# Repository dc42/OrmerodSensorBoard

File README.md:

OrmerodSensorBoard
==================

Here are the design files for my Z-height sensor board add-on to the RepRapPro Ormerod 3D printer. This board replaces the original IR sensor board used for Z-probing. It has the following advantages over the original:

1. It uses modulated infrared light, which makes it much less sensitive to ambient infrared such as is found in sunlight and in incandescent artificial light.
2. The sensor board is mounted on the hot end so that the sensor head is in-line with the nozzle in the x-direction. This makes it much less sensitive to variations in head sag.
3. The board includes the facility to mount the hot end connectors, eliminating the need for the original 6-pin connector. The new connectors are more reliable and more easily disassembled. In particular, the crimp receptacles can more easily be removed from the connector shell.
4. The board can accommodate three Cree LEDs to direct light on the work being printed. Alternatively, it can provide 12V power to an LED strip, or a constant-current supply to external LEDs.
5. The board includes provision for thermostatic control of the hot end fan. The fan is turned on when the hot end temperature exceeds approximately 42C, or when the board detects a hot end temperature measurement fault.
6. The board can also support an experimental ultrasonic sensor. This allows z-probing to be done anywhere on the bed. Due to variation in the speed of sound with temperature, the ultrasonic sensor is a little temperature-sensitive, but this can be compensated in the firmware.

Work is in progress to adapt the board for capacitive height sensing.

For assembly and usage instructions, please visit: http://miscsolutions.wordpress.com/assembling-and-using-the-eschertech-ormerod-hot-end-board/

I supply bare boards, kits of parts with all SMD components ready-mounted, and fully assembled boards. Contact me via the RepRap Ormerod forum at http://forums.reprap.org/list.php?340 by sending a personal message to dc42.

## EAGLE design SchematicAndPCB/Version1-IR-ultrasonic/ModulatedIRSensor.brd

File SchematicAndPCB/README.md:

Licence and copyright
=====================

Copyright (c) 2015 Escher Technologies Limited. Licensed under the Creative Commons Attribution-NonCommercial 4.0 license.
See https://creativecommons.org/licenses/by-nc/4.0/legalcode for a copy.

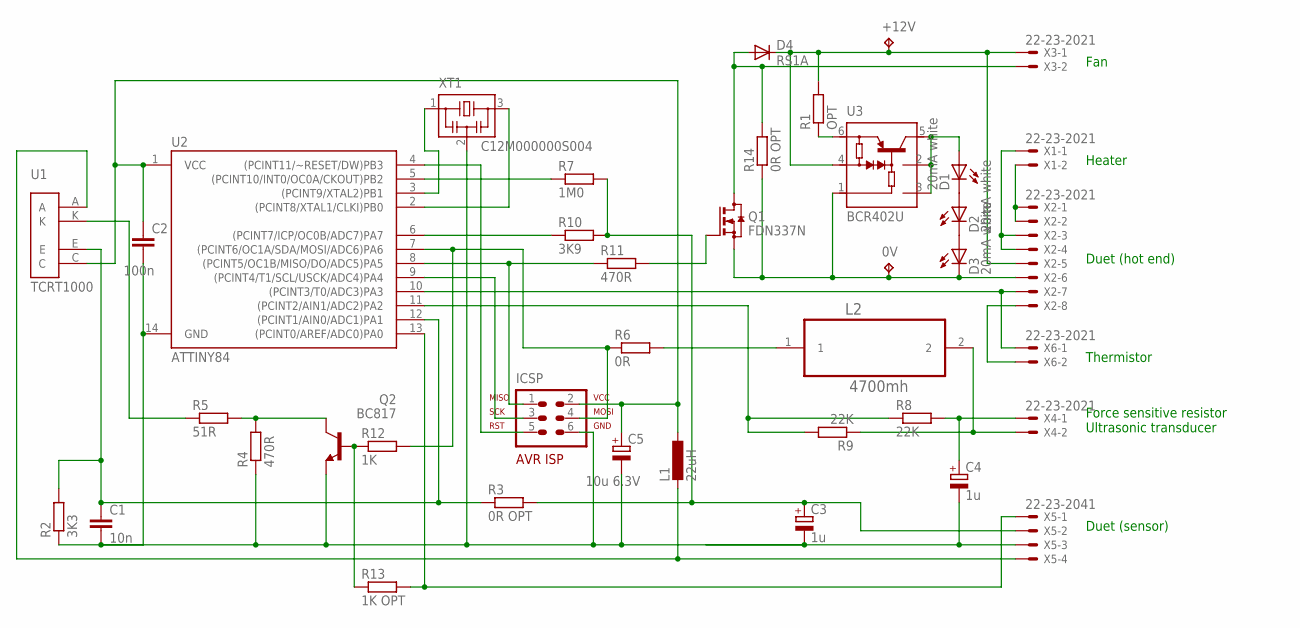
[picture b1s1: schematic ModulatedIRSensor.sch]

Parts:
0V: TPPAD1-13; P1-13
+12V: TPPAD1-13; P1-13
C1: 10n; C0603
C2: 100n; C0603
C3, C4: 1u; SMC_A
C5: 10u 6.3V; SMC_A
D1, D2, D3: 20mA white; LED5MM
D4: RS1A; DO214AC
ICSP: AVR-ISP-6VERT; AVR-ISP-6
L1: 22uH; L2012C
L2: 4700mh; INDC5650X530N
Q1: FDN337N; SOT23
Q2: BC817; SOT23
R1: OPT; R0603
R2: 3K3; R0603
R3, R14: 0R OPT; R0603
R4, R11: 470R; R0603
R5: 51R; R0603
R6: 0R; R0603
R7: 1M0; R0603
R8, R9: 22K; R0603
R10: 3K9; R0603
R12: 1K; R0603
R13: 1K OPT; R0603
U1: TCRT1000
U2: ATTINY84; SO14
U3: BCR402U; SC74_INFINEON
X1, X3, X4, X6: 22-23-2021
X2: 22-23-2021; 22-23-2081
X5: 22-23-2041
XT1: C12M000000S004; CSTCR6M

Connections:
GND: C1.2, C2.2, C3.-, C4.-, C5.-, ICSP.6, Q2.2 (E), R2.1, R4.1, U2.14 (GND), X5.3, XT1.2
GND2: 0V.TP, D3.K (C), Q1.2 (S), R14.1, U3.1 (GND), X2.6
LED: D1.A, U3.2 (IOUT2), U3.3 (IOUT3), U3.5 (IOUT1)
unnamed: L1.2, U1.A, X5.4
unnamed: L2.2, R9.1, X4.2
unnamed: ICSP.5, U2.4 ((PCINT11/~RESET/DW)PB3)
unnamed: ICSP.1, R11.1, U2.8 ((PCINT5/OC1B/MISO/DO/ADC5)PA5)
unnamed: ICSP.3, U2.9 ((PCINT4/T1/SCL/USCK/ADC4)PA4)
unnamed: ICSP.4, R6.1, R12.2, U2.7 ((PCINT6/OC1A/SDA/MOSI/ADC6)PA6)
unnamed: R1.1, U3.6 (REXT)
unnamed: D1.K (C), D2.A
unnamed: U2.10 ((PCINT3/T0/ADC3)PA3), X2.7, X6.1
unnamed: X1.2, X2.1, X2.2
unnamed: D2.K (C), D3.A
unnamed: C3.+, R3.2, R7.2, R10.2, X5.2
unnamed: D4.A, Q1.3 (D), R14.2, X3.2
unnamed: X1.1, X2.3, X2.4
unnamed: X2.8, X6.2
unnamed: R5.1, U1.K
unnamed: L2.1, R6.2
unnamed: Q2.3 (C), R4.2, R5.2
unnamed: R7.1, U2.5 ((PCINT10/INT0/OC0A/CKOUT)PB2)
unnamed: C4.+, R8.2, X4.1
unnamed: R10.1, U2.6 ((PCINT7/ICP/OC0B/ADC7)PA7)
unnamed: R8.1, R9.2, U2.11 ((PCINT2/AIN1/ADC2)PA2)
unnamed: Q1.1 (G), R11.2
unnamed: Q2.1 (B), R12.1, R13.1
unnamed: C1.1, R2.2, R3.1, U1.E, U2.12 ((PCINT1/AIN0/ADC1)PA1)
unnamed: R13.2, U2.13 ((PCINT0/AREF/ADC0)PA0), X5.1
unnamed: U2.2 ((PCINT8/XTAL1/CLKI)PB0), XT1.3
unnamed: U2.3 ((PCINT9/XTAL2)PB1), XT1.1
VCC: C2.1, C5.+, ICSP.2, L1.1, U1.C, U2.1 (VCC)
VS+12V: +12V.TP, D4.C, R1.2, U3.4 (VIN), X2.5, X3.1

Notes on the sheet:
Heater
Duet (hot end)
Thermistor
Duet (sensor)
Force sensitive resistor Ultrasonic transducer
Fan
TCRT1000

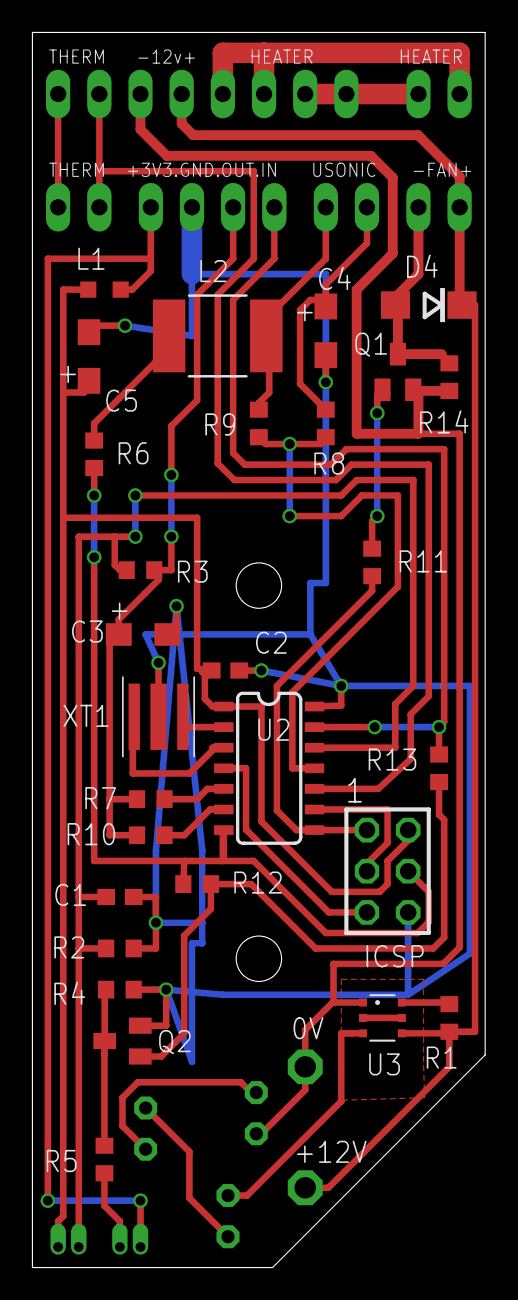
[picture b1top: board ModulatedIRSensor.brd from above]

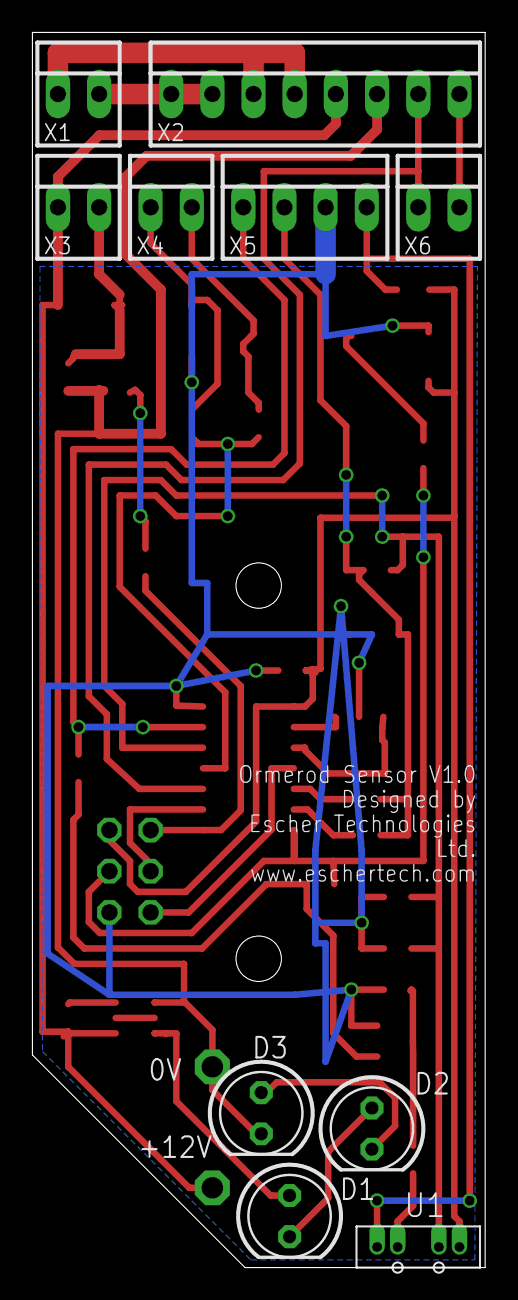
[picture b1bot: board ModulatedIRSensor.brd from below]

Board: 2 copper layers, 27.9 x 76.2 mm, 40 parts (12 on the bottom side), 33 nets.

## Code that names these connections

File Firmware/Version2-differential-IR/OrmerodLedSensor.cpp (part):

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#endif

#define DUAL_NOZZLE (1)		// set nonzero for dual nozzle support
#define ISR_DEBUG	(0)		// set nonzero to use PB2 as debug output pin

#if DUAL_NOZZLE && ISR_DEBUG
#error "DUAL_NOZZLE and ISR_DEBUG may not both be set"
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#define BITVAL(_x) static_cast<uint8_t>(1u << (_x))

// Pin assignments:
// PA0/ADC0		digital input from Duet
// PA1/ADC1		analog input from phototransistor
// PA2/ADC2		output to Duet via 12K resistor (single nozzle) OR analog input from thermistor2 (dual nozzle)
// PA3/ADC3		analog input from thermistor (single nozzle) or 1K/4K7 sense pin (dual nozzle)
// PA4/SCLK		1K/4K7 sense pin (single nozzle) or analog input from thermistor 1 (dual nozzle). Also SCLK when programming.
// PA5/OC1B		digital output to control fan, active high. Also MISO when programming.
// PA6/OC1A		near LED drive, active low in prototype, will be active high in release. Also MOSI when programming.
// PA7/OC0B		output to Duet via 10K resistor

// PB0			far LED drive, active high
// PB1			far LED drive, active high (paralleled with PB0)
// PB2/OC0A		unused (single nozzle) OR ISR-DEBUG pin OR output to Duet via 12K resistor (dual nozzle)
// PB3/RESET	not available, used for programming

__fuse_t __fuse __attribute__((section (".fuse"))) = {0xE2u, 0xDFu, 0xFFu};

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
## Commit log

2014-03-16 Added STL files
    Added STL files for the printed parts needed to use the new sensor
    board, along with some other printed parts for the Ormerod
2014-03-16 Replaced readme.txt by readme.md
2014-03-16 Added schematic, board layout and circuit notes
2014-03-20 Added fan deflector aerofoil
2014-03-22 Added firmware files
2014-03-24 Added new parts
2014-03-26 Updated BOM
2014-03-27 Added insulator that holds ultrasonic transducer
2014-03-27 Update readme.md
    Added description of insulator with holder for the ultrasonic transducer
2014-03-28 Changed insulator for ultrasonic transducer
    Modified the design of the insulator with a holder for the ultrasonic
    transducer to reduce the depth of the countersink, so that the screws
    only protrude 3mm beyond the back of the PCB. Added a cutout to allow
    in-situ programming.
2014-04-04 Added sensorpad.scad and .stl
2014-04-04 Added description of sensorpad.stl to readme file
2014-05-04 Added modified sensor pad and button push
    Added a modified version of the add-on sensor pad that places the homing
    tab nearer the z-screw and avoids fouling the z stepper motor shaft
2014-05-29 Added cutout to access ICSP contacts
    Added a cutout to the insulator so that the ICSP contacts for
    reprogramming the mcu can be accessed in-situ.
2014-05-29 Added capsense variant of the insulator
    Added a variant of the sensor board insulator to suit the prototype
    (hacked) capacitive height sensing board
2014-05-29 Add X-carriage design
    Added .scad and .stl files for Ormerod X-carriage
2014-06-19 Added sensor pad for diff IR sensor
    Also deleted some obsolete files
2014-06-20 Various parts updated
    Reduced tab width for differential IR sensor pad
    Adjusted spacing for differential IR sensor board holder
    Tidied up fan inlet duct and made some dimensions configurable
2014-06-23 Added nozzle mount
2014-06-24 Added differential LED board schematic
2014-06-24 Nozzle mount now configured for 2 nozzles
2014-06-26 Added revised modified heatsink duct
    Added new version of modified heatsink duct based on importing RRP's
    original one into OpenScad. Also made sensor pad 1mm wider.
2014-07-04 Rearranged folders and added diff LED firmware
2014-07-04 Added differential LED sensor circuit notes
2014-07-10 Corrected nozzle mount and added fan duct
    Increased the size of the slots in the nozzle mount to clear the brass
    Bowden end
    Added modified-fan-duct, which is RRP's fan duct with the cable tie loop
    cut off (the cable tie loop gets in the way of my hot end board)
2014-07-10 Added first attempt at Duet+Duet4X enclosure
2014-07-10 Corrections to Duet_X4 enclosure
    Moved X4 lower standoffs an extra 2mm apart to match X4 board
    Increased Duet standoff radius by 0.1mm because slic3r was generating 2
    circles to print it instead of 3
    Added extra 1mm clearance for ribbon cable at top of box when X4 option
    is enabled
2014-07-11 Minor corrections to Duet+X4 enclosure
2014-07-11 Added options for dual nozzle conversion
    Added options to the modified heatsink duct and the insulator to suit
    the dual nozzle conversion. The standoffs on the heatsink duct for
    fitting the sensor board need to be deeper for the dual nozzle, to give
    adequate clearance between the sensor components and the nearer of the
    two heater blocks. The insulator pillars are made thinner to compensate
    in part.
2014-07-14 Corrected insulator countersinks with short pillars
    Corrected the differential LED sensor insulating plate so that when the
    pillars are very short (e.g. with the dual nozzle option selected), the
    countersinks for the mounting screws are in the right place
2014-07-14 Corrections for X4 variant
    Increased board depth so that the lid should fit
    Adjusted positions of cutouts for Duet connectors and SD card
2014-07-18 Amended nozzle mount to support 3 cutouts
    The nozzle mount now supports 3 cutouts so that it can be used with
    single nozzle heads (with modified heatsink block) and dual nozzle
    heads. Also increased side of Bowden slots a little.
2014-07-26 Added an angle to the nozzle mount
    Changed the nozzle mount design to allow it to be angled to correct for
    head sag
2014-08-04 Improved enclosure design + long nozzle mount option
    Improved the Duet+X4 enclosure design by strengthening the mounting
    pillars and adding access holes for the X4 power terminal screws. Also
    added an option on the nozzle mount to make it long, to help get started
    with ABS printing.
2014-08-06 Added 'long' option to go with long nozzle mount
2014-08-14 Fan deflector now has 4 screw holes
    Added 2 more screw holes to the fan deflector. This allows 4 mounting
    screws to be used to hold the fan to the heatsink, to avoid distorting
    the fan, which can make it noisy.
2014-08-14 Added modified version of iambury's extruder gears
    Added a version of iamburny's double helix extruder gears, modified to
    make the holes for the motor shaft and the hex bolt customisable. Before
    I did this and increased the sizes, I found they were too tight to fit
    on the motor and the bolt.
2014-08-18 Updated button push
    Updated the button push model to make the lengths configurable.
    Increased the default length to work with the Duet+DueX4 enclosure.
2014-09-03 Added standard nozzle mount
2014-09-08 Create LICENSE
2014-10-05 Added files
2014-10-15 Added heatsink duct with board lowered by another 0.5mm
2014-10-28 Updated schematic and firmware for 2 nozzle
    Added the schematic for the 2-nozzle board. Updated the firmware source
    code to support the 2-nozzle board.
2015-01-06 Improved some models
    Improved model of Duet enclosure for Mini Kossel, and checked in some
    changes to iamburny's extruder gears
2015-05-05 Updated firmware for dual board
    Updated the firmware for the dual nozzle board to use the same offset
    cancellation technique as the single nozzle board when reading the
    thermistors. Reduced the number of thermistor samples averaged for the
    dual board to avoid running out of RAM. Also added holders for dual
    nozzle and mini boards.
2015-05-05 Added orthogonal calibration piece
    Added a configurable orthogonal calibration piece so that it can be made
    small enough to use on the Mini Kossel
2015-05-05 Added STL for the orthogonal calibration piece
2015-05-06 Added mini differential IR schematic and firmware
2015-06-09 New modulation order
    Changed modulation order to avoid an additional false trigger height
    above white surfaces following increase in sensitivity to better work
    with BuildTak as a target
2016-01-20 Updated firmware and schematic to version 1.1a
    Updated the firmware and schematic to correspond with version 1.1a
    production boards

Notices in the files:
parts and their libraries:
SparkFun-DigitalIC: Licensing: CC v3.0 Share-Alike You are welcome to use this library for commercial purposes.
